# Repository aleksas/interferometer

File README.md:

# Current version does not work due to critical errors in schematics

# Self mixing interferometer
Schematic designs and theoretical simulation to aid in building a self mixing optical interferometer.
Theoretical explanation of pcb purpose and circuit part choices explained in [this document](./documents/Laser_diode_modulation.pdf) (skip simulation details). 

General idea is explained in [the video](https://youtu.be/MUdro-6u2Zg?t=1291). More in depth eplanation can be found at least in [this publication](https://scihub.bban.top/10.1364/AOP.7.000570).

Main motivation is to develope a convinient device toplay around with self mixing interferometry. It provides significant improvement in precision over [ToF distance estimation](https://en.wikipedia.org/wiki/Time-of-flight_camera) ([Arduino ToF sensor](https://osoyoo.com/2019/04/21/arduino-lesson-vl53l0x-time-of-flight-distance-sensor/)). Apart from using in objct distance and speed estimation it also can be usefull for harmonic motion measurements, e.g. submicron vibrations.  

## Plan
- [ ] Update [current arduino shield](./pcb/) to make convinient self-mxing laser interferometry easily accesible
  - [ ] __Laser diode current modulation__
    - [ ] (Optional) Reproduce convinient SPICE simulation from [document (p. 34)](./documents/Laser_diode_modulation.pdf)
    - [x] Prepare board for convinient pcb manufacturing
      Capacitors, resistors, leds are loosely defined. Missing voltage and maybe other parameters. Entries like ARDUINO_SHIELD or measuring points only add to the confusion.  
      - [EasyEda](https://easyeda.com/aleksas_/self-mixing-laser-interferometer) | [LCSC](https://lcsc.com/)
    - [x] Optional: update [KiCAD model](./pcb/)
      - so that it visualizes electronic components in 3D
      - doesn't depend on deprecated symbols
    - [x] Assess the modulation frequency of ADN8810
      - [~333 kHZ](https://electronics.stackexchange.com/a/497173/249362)
    - [ ] Assess the probable performace of the board
      - [ ] Controlled by [Arduino DUE](https://www.arduino.cc/en/Guide/ArduinoDue) (preferred)
        - [ ] What is maximum laser diode modulation frequencynoredirect=1#comment1266315_497173)
        - [ ] What is the maximum precision of modulated current 
      - [ ] Controlled by [STM32F4DISCOVERY](https://www.st.com/en/evaluation-tools/stm32f4discovery.html)
        - [ ] What is maximum laser diode modulation frequency
        - [ ] What is the maximum precision of modulated current     
  - [ ] __Physical printed and assemled board validation__
    - [x] Assemble board and connect to Arduino or arduino form factor development board
    - [x] Write [software to control PCB laser diode modulation](./arduino/Uno_R3/modulation/modulation.ino)
      - [Code for modulatin ADN8810 from arduino](https://github.com/analogdevicesinc/arduino/blob/486ce99954853b3e9f34e81e827f400b49ca4765/Arduino%20Uno%20R3/examples/CN0395_example/ADN8810.cpp#L117-L140)
      - [Arduino SPI Barometric Pressure Sensor](https://www.arduino.cc/en/Tutorial/BarometricPressureSensor)      
      - [Some code](./arduino)
    - [ ] Verify laser diode modulation input
    - [ ] Verify laser monitor diode signal has interference pattern
  - [ ] __Estimating values form monitor diode signal__
    - Arduino ADC (current solution implemented on PCB) or FPGA
- [ ] Software for theoretical signal simulation and distance,velocity estimation
  - [ ] [Python scripts for simulating and estimatimating values](https://gist.github.com/aleksas/e764e93894b7945427d594147ea23370)
    - [x] Distance to stationary object
    - [x] Distance and velocity of moving/stationary object
    - [ ] Velocity of moving object having noisy signal

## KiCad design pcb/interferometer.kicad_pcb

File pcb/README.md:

The implementation chosen is self mixing interferometry as the diode lasers were readily available therefore provided a good starting point to the approach chosen 
of self mixing interferometry. Includes design of a CW diode LASER driver, 
a transimpedance amplifier on the Photodiode section of the TO-18 laser diode with a -3dB cutoff of 200 kHz, 
an output high pass filter and the relevant control circuitry that allows the whole system to be tested and controlled with industry standard 32 bit, 
arduino form factor development boards such as the FREEDOM© series from NXP or the DISCOVERY© and NUCLEO© series from STMicroelectronics among others.

[Interactive 3D preview](https://aleksas.github.io/interferometer)

## PCB Components

### [ADN8810 (ADN8810ACPZ)](https://www.analog.com/en/products/adn8810.html?doc=ADN8810.pdf) - 12-Bit High Output Current Source [by Analog Devices](https://www.analog.com/)
- [Data Sheet](datasheets/ADN8810.pdf) ([source](https://www.analog.com/media/en/technical-documentation/data-sheets/ADN8810.pdf))
- [Vendors](https://octopart.com/adn8810acpz-analog+devices-433821?r=sp)

### [OPA320 (OPA320SAIDBVT)](https://www.ti.com/product/OPA320) - Precision, 20-MHz, 0.9-pA, Low-Noise, RRIO, CMOS Operational Amplifier With Shutdown by [Textas Instruments](https://www.ti.com/)
- [Data Sheet](datasheets/opa320.pdf) ([source](https://www.ti.com/lit/ds/symlink/opa320.pdf?ts=1592210569432))
- [PSpice](spice/OPA320.LIB) ([source](https://www.ti.com/lit/zip/sbom437))
- [Vendors](https://octopart.com/search?q=OPA320SAIDBVT&currency=USD&specs=0)

### [ADR292 (ADR292GRUZ)](http://www.analog.com/ADR292) - Low Noise Micropower 4.096 V Precision Voltage Reference [by Analog Devices](https://www.analog.com/)
- [Data Sheet](datasheets/ADR291_292.pdf) ([source](https://www.analog.com/media/en/technical-documentation/data-sheets/ADR291_292.pdf))
- [Vendors](https://octopart.com/search?q=ADR292GRUZ&currency=USD&specs=0)

### Laser
#### ADL-65055TL - N-Type ALGalnP Visible Laser Diode by [Laser Comonents](https://www.lasercomponents.com/)/[Arima Lasers](https://www.arimalasers.com/)
- [Data Sheet](datasheets/adl-65055tl.pdf) (sources: [1](https://www.lasercomponents.com/fileadmin/user_upload/home/Datasheets/arima/655nm/adl-65055tl.pdf), [2](http://www.farnell.com/datasheets/43655.pdf?_ga=2.22848763.1942577091.1592211693-817925239.1592211693), [3](http://www.farnell.com/datasheets/43655.pdf))
- [PSpice](spice/ADL65055TL.lib) ([source](https://www.eit.lth.se/sprapport.php?uid=824))
- [Vendors](https://octopart.com/2008361-laser+components-23943555?r=sp)

#### LTLD505T - Laser Diode 650nm 2.6VDC AlGaInP Laser Diode by [Lite-On Electronics](https://www.liteon.com/)
- [Data Sheet](datasheets/LTLD505T.pdf) ([source](https://www.jameco.com/Jameco/Products/ProdDS/2120428.pdf))
- [Vendors](https://octopart.com/ltld505t-lite-on-18796936?r=sp)

### [FDC637BNZ](https://www.onsemi.com/products/discretes-drivers/mosfets/fdc637bnz) - N-Channel 2.5V Specified PowerTrench MOSFET by [ON Semiconductor](https://www.onsemi.com)
- [Data Sheet](datasheets/FDC637BNZ-D.pdf) ([source](https://www.onsemi.com/pub/Collateral/FDC637BNZ-D.pdf))
- [PSpice](spice/FDC637BNZ.lib) ([source](https://www.onsemi.com/pub/Collateral/FDC637BNZ.lib))
- [Vendors](https://octopart.com/fdc637bnz-on+semiconductor-84325753?r=sp)

## References
- [Original project by Kiogora](https://github.com/Kiogora/interferometer)
  - [Whitepaper](https://github.com/aleksas/interferometer/raw/master/documents/Laser_diode_modulation.pdf)

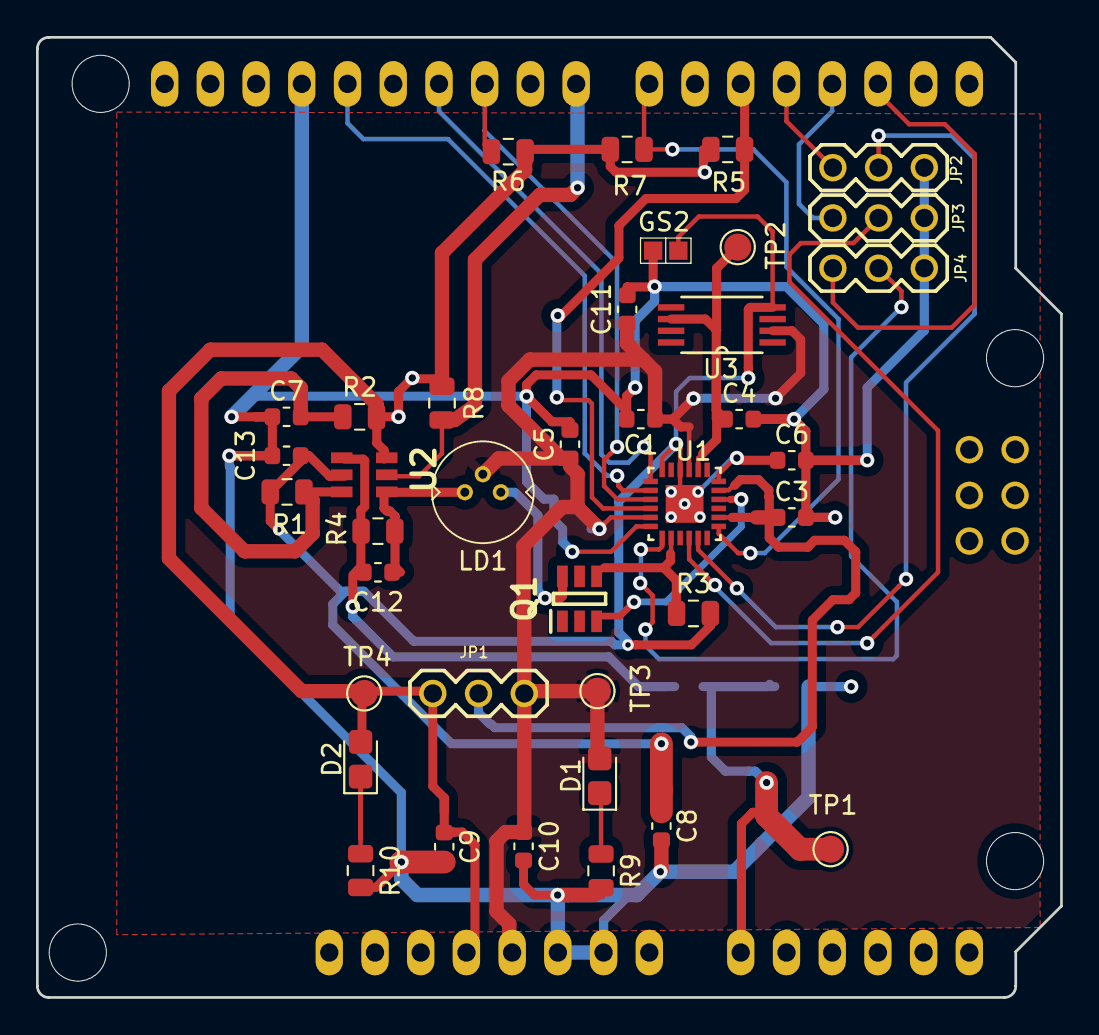
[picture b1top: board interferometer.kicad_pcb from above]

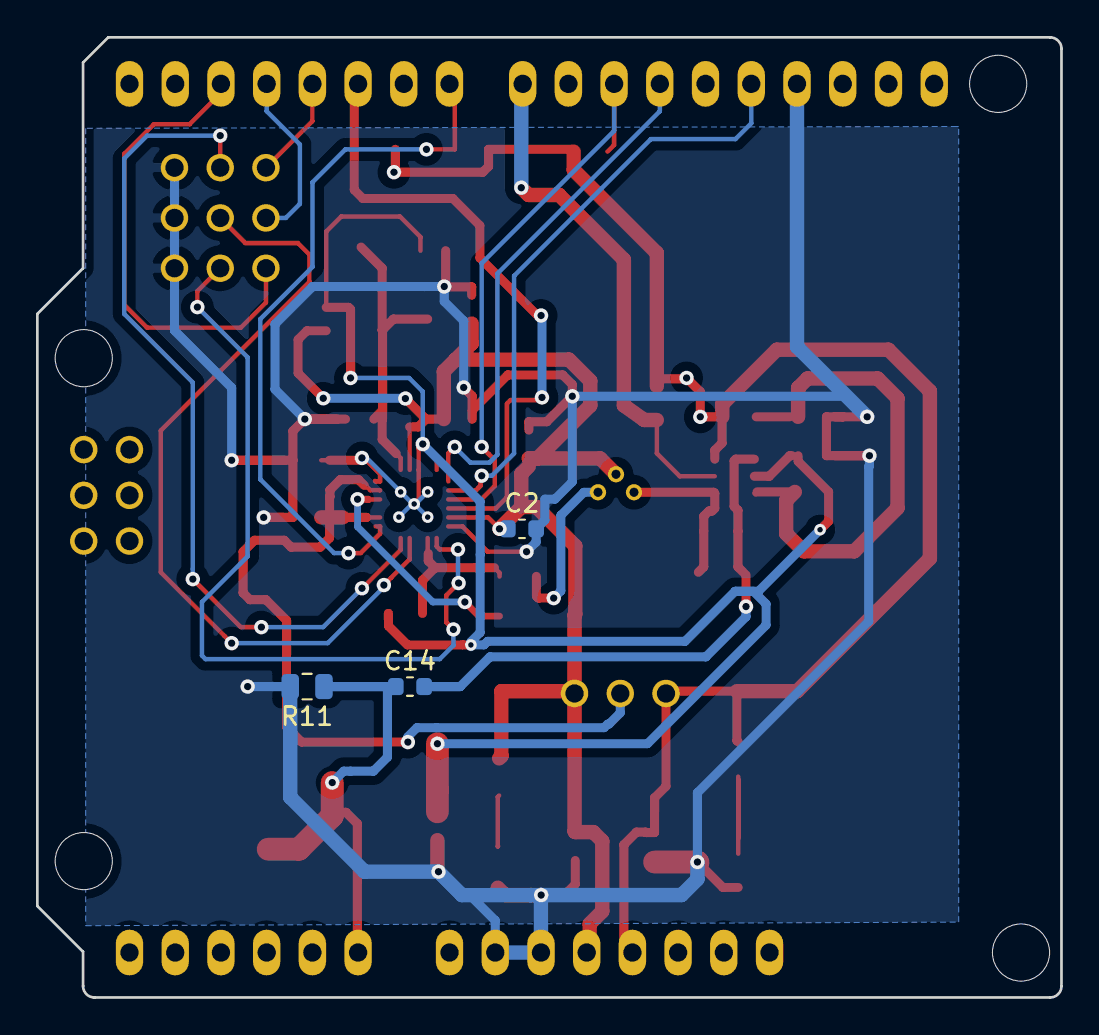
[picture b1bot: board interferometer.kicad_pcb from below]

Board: 2 copper layers, 56.9 x 53.3 mm, 42 parts (3 on the bottom side), 27 nets.

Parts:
C1, C2, C3, C4, C5, C6, C7, C11, C13, C14: 0.1uF; C_0603_1608Metric
C8, C9, C10: 22uF; C_0603_1608Metric
C12: 82pF; C_0603_1608Metric
D1, D2: LED; LED_0805_2012Metric_Castellated
J1: GS2
JP1, JP2, JP3, JP4: Jumper_NC_Dual; 1X03
LD1: Laserdiode_N_TYPE; ADL-65055TL
Q1: FDC637BNZ; SOT95P280X145-6N
R1: 680k; R_0805_2012Metric
R2: 21k; R_0805_2012Metric
R3: 66.5R; R_0805_2012Metric
R4: 7.87k; R_0805_2012Metric
R5, R6, R7, R8: 100k; R_0805_2012Metric
R9: 220R; R_0805_2012Metric
R10: 100R; R_0805_2012Metric
R11: 5.1k; R_0805_2012Metric
SHIELD1: ARDUINO_SHIELD
TP1, TP2, TP3, TP4: TESTPOINT; TestPoint_Pad_D1.5mm
U1: ADN8810ACPZ
U2: OPA320SAIDBVT; SOT95P280X145-6N
U3: ADR292GRUZ

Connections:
/3v3: C9.1, D2.2, JP1.3, R2.1, R5.1, R6.1, R7.1, R8.1, SHIELD1.3V3, TP4.1, U2.6
/4.096_VREF: C4.1, TP2.1, U1.14, U3.6
/5v: C1.1, C2.1, C5.1, C10.1, C11.1, D1.2, JP1.1, LD1.2, SHIELD1.5V, TP3.1, U1.15, U1.23, U3.2
/A0: C14.1, R11.1, SHIELD1.AD0, TP1.1
/ADDR0: JP2.3, SHIELD1.4
/ADDR1: JP3.3, SHIELD1.3
/ADDR2: JP4.3, SHIELD1.2
/AVSS: C6.1, C8.1, C13.1, J1.1, R1.1, R3.2, U1.12, U1.16, U1.18, U1.25, U2.2, U3.4
/IOUT: Q1.3, U1.10
/LD: LD1.1, Q1.6
/MOSI: SHIELD1.11, U1.19
/PD: C12.2, LD1.3, R4.2, U2.4
/RSN: Q1.4, R3.1, U1.2
/SCK: SHIELD1.13, U1.20
/chip_addr0: JP2.2, U1.5
/chip_addr1: JP3.2, U1.4
/chip_addr2: JP4.2, U1.1
/~CS: R6.2, SHIELD1.10, U1.21
/~SHDN: R8.2, SHIELD1.8, U2.5
/~laser_reset: R5.2, SHIELD1.5, U1.22
/~laser_standby: R7.2, SHIELD1.7, U1.7
Earth: C1.2, C2.2, C3.2, C4.2, C5.2, C6.2, C7.1, C8.2, C9.2, C10.2, C11.2, C13.2, J1.2, JP2.1, JP3.1, JP4.1, R9.2, R10.2, R11.2, SHIELD1.GND1, SHIELD1.GND2, SHIELD1.GND3, U1.24
unnamed: C3.1, JP1.2, U1.8, U1.11
unnamed: C7.2, R1.2, R2.2, U2.3
unnamed: C12.1, C14.2, R4.1, U2.1
unnamed: D1.1, R9.1
unnamed: D2.1, R10.1

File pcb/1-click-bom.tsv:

References	Qty	Description	Manufacturer	MPN	Manufacturer	MPN	Manufacturer	MPN	Digikey	Mouser	RS	Newark	Farnell	LCSC
C1, C2, C3, C4, C5, C6, C7, C11, C13, C14,	10	100nF 5% Capacitors_SMD:C_0805_HandSoldering	Samsung Electro-Mechanics	CL21B104JBCNNNC										C62912
C8, C9, C10,	3	22uF Capacitors_SMD:C_1210_HandSoldering			Taiyo Yuden	TMK325BJ226KM-P								C268020
C12,	1	82pF Capacitors_SMD:C_0805_HandSoldering	Samsung Electro-Mechanics	CL21C820JBANNNC										C170103
D1, D2,	2	LED LEDs:LED_0805	Lite-On	LTST-C171KGKT										C98224
JP1, JP2, JP3, JP4,	4	Jumper_NC_Dual freetronics_footprints:1X03												
LD1,	1	Laserdiode_N_TYPE ADN8810ACPZ:ADL-65055TL	LASER COMPONENTS	ADL-65055TL									1272658	
Q1,	1	50V Vds, 0.22 A Id, N-channel MOSFET, SOT-23	ON Semiconductor	FDC637BNZ					FDC637BNZCT-ND	512FDC637BNZ		95W3155	2322581	C68302
R1,	1	680KOhms 0.5% Resistors_SMD:R_0805												C422818
R2,	1	21KOhms 1% Resistors_SMD:R_0805			LIZ Elec	CR0805F82102G	UNI-ROYAL(Uniroyal Elec)	0805W8F2102T5E						C17550
R3,	1	66.5Ohms 1% Resistors_SMD:R_0805	Panasonic	ERJ-6ENF66R5V										C410033
R4,	1	7.87KOhms 1% Resistors_SMD:R_0805												C17810
R5, R6, R7, R8,	4	100KOhms 0.1% Resistors_SMD:R_0805_HandSoldering	Panasonic	ERA-6AEB104V					P100KDACT-ND	667ERA6AEB104V 	566765	01X1346	1577686	C55868
R9,	1	220Ohms 0.1% Resistors_SMD:R_0805_HandSoldering												C17557
R10,	1	100Ohms 0.5% Resistors_SMD:R_0805_HandSoldering												C42959
R11,	1	5.1KOhms 0.5% Resistors_SMD:R_0805_HandSoldering	Panasonic	ERJ-6RBD5101V										C336831
U1,	1	ADN8810ACPZ ADN8810ACPZ:ADN8810ACPZ	Analog Devices	ADN8810ACPZ					ADN8810ACPZ-ND	584ADN8810ACPZ	7089833	27X8183	2377083	
U2,	1	Dual CMOS Operational Amplifiers, Zero-Drift Series, 1.8-V, microPower	Texas Instruments	OPA320SAIDBVT					296-36434-1-ND	595OPA320SAIDBVT		33AH4590	3004957	
U3,	1	ADR292GRUZ ADN8810ACPZ:ADR292GRUZ	Analog Devices	ADR292GRUZ					ADR292GRUZ-ND	584ADR292GRUZ	7098168	14AC3018	2727741

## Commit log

2017-05-18 Add simulation gifs
2017-05-18 Add python scripts
2017-05-18 Modify schematic
2017-05-21 Modify design
2017-05-21 finalise layout
2017-05-21 Output gerbers
2017-05-21 Output gerbers(protel file extensions)
2017-05-21 design postprocessing
2017-05-21 Add 3D view gif
2017-05-22 modify design for manufacturing
2020-04-20 Update project. Cleanup.
2020-04-23 cleanup
2020-04-26 fix farnell part nmber
2020-04-29 fill missing vendors
2020-05-01 Board updated by fiverr.com:Saqibchaudhr141
2020-05-20 Update animation.
2020-05-28 Add missing packages3d.
2020-05-28 Cleanup.
2020-05-28 add arduino code
2020-06-15 Add datasheets
2020-06-15 Update datasheets
2020-06-15 Add PSpice links
2020-06-15 Add spice models
2020-06-15 Cleanup. Add spice models.
2020-06-15 Kitspace path update.
2020-06-19 Add liteon laser diode datasheet
2020-07-19 Update modulation
